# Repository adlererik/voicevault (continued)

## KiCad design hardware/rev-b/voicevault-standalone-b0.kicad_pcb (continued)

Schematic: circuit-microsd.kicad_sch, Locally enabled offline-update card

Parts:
C401: 2.2u 10V; C_0603_1608Metric
C402: 10u 10V; C_0805_2012Metric
C403, C404, C405: 100n 10V; C_0402_1005Metric
J401: 1040310811; microSD_HC_Molex_104031-0811
R401, R402: 100k; R_0402_1005Metric
R403, R404, R405, R406, R407: 47k; R_0402_1005Metric
U401: TLV75533PDRVR; TI_DRV0006A_WSON6_2x2_EP1x1p6
U402: SN74AXC4T774PWR; TSSOP-16_4.4x5mm_P0.65mm

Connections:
GND: C401.2, C402.2, C403.2, C404.2, C405.2, J401.6 (VSS), J401.10 (DETECT_GND), J401.SH (SHELL), R401.2, U401.3 (GND), U401.7 (EP_GND), U402.7 (DIR3), U402.10 (GND); also elsewhere on the board
SD_3V3: C402.1, C403.1, C405.1, J401.4 (VDD), R403.2, R404.2, R405.2, R406.2, U401.1 (OUT), U402.15 (VCCB); also elsewhere on the board
SD_CS_MCU: U402.6 (A4); also elsewhere on the board
SD_CS_N: J401.2 (DAT3_CS), R403.1, U402.11 (B4)
SD_DAT1: J401.8 (DAT1), R404.1
SD_DAT2: J401.1 (DAT2), R405.1
SD_DETECT_N: J401.9 (DETECT), R407.1; also elsewhere on the board
SD_IO_DISABLE: R402.1, U402.9 (OE_N); also elsewhere on the board
SD_MISO: J401.7 (DAT0_MISO), U402.12 (B3)
SD_MISO_MCU: U402.5 (A3); also elsewhere on the board
SD_MOSI: J401.3 (CMD_MOSI), R406.1, U402.13 (B2)
SD_MOSI_MCU: U402.4 (A2); also elsewhere on the board
SD_POWER_EN: R401.1, U401.4 (EN); also elsewhere on the board
SD_SCK: J401.5 (CLK), U402.14 (B1)
SD_SCK_MCU: U402.3 (A1); also elsewhere on the board
VDD_3V3: C404.1, R402.2, R407.2, U402.1 (DIR1), U402.2 (DIR2), U402.8 (DIR4), U402.16 (VCCA); also elsewhere on the board
VSYS: C401.1, U401.6 (IN); also elsewhere on the board

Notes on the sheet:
Card uses software SPI on dedicated MCU GPIO; no radio/shared trusted bus access.
Power and signal bridge default off. Enable card power, verify settle, then enable signals only in local update mode.
Reject unsigned, wrong-target and rollback images on the trusted MCU; card data remains untrusted.
LDO is specified for 500mA but thermal/current/battery limits and card peak current still require bench qualification.
Card-detect switch stays in trusted 3.3V domain; it is mechanically isolated from SD power.

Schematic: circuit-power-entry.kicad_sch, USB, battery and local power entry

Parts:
C501: 100n 16V; C_0402_1005Metric
C502: 100n 10V; C_0402_1005Metric
D501, D502: PMEG2010ER,115; Nexperia_CFP3_SOD-123W
D503: SMF5.0A; D_SOD-123F
F501: MF-PSMF050X-2; Fuse_0805_2012Metric
J501: USB4125-GF-A; USB_C_Receptacle_GCT_USB4125-xx-x_6P_TopMnt_Horizontal
J502: S2B-PH-SM4-TB(LF)(SN); BATTERY; JST_PH_S2B-PH-SM4-TB_1x02-1MP_P2.00mm_Horizontal
J503: BM02B-SRSS-TB(LF)(SN); EXTERNAL NTC; JST_SH_BM02B-SRSS-TB_1x02-1MP_P1.00mm_Vertical
SW503: TL3305AF160QG; POWER; SW_SPST_TL3305A

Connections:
BAT_NTC: J503.1 (NTC); also elsewhere on the board
BAT_PACK: C502.1, J502.1 (PACK_PLUS); also elsewhere on the board
BTN_POWER: SW503.1 (SHPHLD); also elsewhere on the board
GND: C501.2, C502.2, D503.2 (A), J501.A12 (GND), J501.B12 (GND), J501.SH (SHELL), J502.2 (PACK_MINUS), J503.2 (GND), SW503.2 (GND); also elsewhere on the board
PMIC_VBUS: C501.1, D501.1 (K), D502.1 (K); also elsewhere on the board
QI_5V: D502.2 (A); also elsewhere on the board
USB_5V_FUSED: D501.2 (A), D503.1 (K), F501.2 (OUT)
USB_5V_RAW: F501.1 (IN), J501.A9 (VBUS), J501.B9 (VBUS)
USB_CC1: J501.A5 (CC1); also elsewhere on the board
USB_CC2: J501.B5 (CC2); also elsewhere on the board

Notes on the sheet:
USB4125 has power/CC only: no USB data connection to trusted MCU. Power USB is for a trusted bench source.
USB/Qi Schottky OR prevents direct source paralleling; input allowance includes voltage drop, fuse derating and heat.
nPM1300 supplies CC pull-downs internally; do not add parallel 5.1k resistors.
External 10k NTC with configured beta must be thermally attached to the battery. Missing/invalid NTC must inhibit charging.
Battery is a protected external assembly. Verify actual connector polarity before power; no battery included in PCB assembly BOM.

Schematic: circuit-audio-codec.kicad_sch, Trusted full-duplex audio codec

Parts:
C601, C602, C603, C605: 10u 10V; C_0805_2012Metric
C604, C606, C607, C608: 100n 10V; C_0402_1005Metric
D601: BAT54WS; DLDO to ALDO pop suppression; D_SOD-323
R601, R602: 2.2k; R_0402_1005Metric
R603: 100k; R_0402_1005Metric
U601: TLV320AIC3204IRHBR; QFN-32-1EP_5x5mm_P0.5mm_EP3.45x3.45mm

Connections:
AUD_ADC_DATA: U601.5 (DOUT); also elsewhere on the board
AUD_AVDD_1V8: C601.1, C607.1, D601.1 (K), U601.24 (AVDD_ALDO_OUT)
AUD_BCLK: U601.2 (BCLK); also elsewhere on the board
AUD_DAC_DATA: U601.4 (DIN); also elsewhere on the board
AUD_DVDD_1V72: C602.1, C608.1, D601.2 (A), U601.29 (DVDD_DLDO_OUT)
AUD_HPL_DC: U601.25 (HPL); also elsewhere on the board
AUD_HPR_DC: U601.27 (HPR); also elsewhere on the board
AUD_LDOIN_3V3: C605.1, C606.1, U601.26 (LDOIN_HPVDD); also elsewhere on the board
AUD_MCLK: U601.1 (MCLK); also elsewhere on the board
AUD_MICBIAS: U601.19 (MICBIAS); also elsewhere on the board
AUD_REF: C603.1, U601.18 (REF)
AUD_RESET_N: R603.1, U601.31 (RESET_N); also elsewhere on the board
AUD_SCL: R601.1, U601.9 (SCL); also elsewhere on the board
AUD_SDA: R602.1, U601.10 (SDA); also elsewhere on the board
AUD_WCLK: U601.3 (WCLK); also elsewhere on the board
GND: C601.2, C602.2, C603.2, C604.2, C605.2, C606.2, C607.2, C608.2, R603.2, U601.7 (IOVSS), U601.8 (SCLK_MFP3), U601.12 (SPI_SELECT_I2C), U601.17 (AVSS), U601.28 (DVSS), U601.33 (EP_GND); also elsewhere on the board
MIC_ADC: U601.13 (IN1_L); also elsewhere on the board
VDD_3V3: C604.1, R601.2, R602.2, U601.6 (IOVDD), U601.30 (LDO_SELECT_INTERNAL); also elsewhere on the board

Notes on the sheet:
TI SLOS602E pins/package; SLAA492A internal DLDO/ALDO sequence with DVDD-to-AVDD Schottky diode.
IOVDD uses VDD_3V3; LDOIN has a separate switched 500mA-capable regulator. LDO_SELECT high enables internal 1.72V DLDO; AVDD/DVDD are not tied to 3.3V.
Hold RESET low while rails settle; wait at least 1ms after reset before writes, enable ALDO at >=DLDO voltage, then ADC/DAC.
SAI1 AF13: PE2 MCLK_A, PE3 SD_B capture, PE4 FS_A, PE5 SCK_A, PE6 SD_A playback.
Audio I2C2 PF0/PF1 and SAI are connected only to the trusted MCU; no radio wires.

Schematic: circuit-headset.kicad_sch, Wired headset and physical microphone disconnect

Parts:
C609: 1u 10V X7R; C_0603_1608Metric
C610: 33p C0G; C_0402_1005Metric
C611, C612: 220u 6.3V polymer; exact MPN qualification pending; CP_EIA-7343-31_Kemet-D
D602, D603, D604: PESD5V0S1BA,115; bidirectional ESD; D_SOD-323
J601: SJ-43514-SMT-TR; CTIA headset; SJ43514SMT
R604: 2.2k 1%; R_0402_1005Metric
R605: 1k 1%; R_0402_1005Metric
R606, R607: 10R 1% 0.1W; R_0402_1005Metric
SW601: JS102011SAQN; physical microphone disconnect; SW_SPDT_CK_JS102011SAQN

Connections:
AUD_HPL_DC: C611.1 (PLUS); also elsewhere on the board
AUD_HPR_DC: C612.1 (PLUS); also elsewhere on the board
AUD_MICBIAS: R604.1; also elsewhere on the board
GND: C610.2, D602.2 (RETURN), D603.2 (RETURN), D604.2 (RETURN), J601.4 (RING2_GND), SW601.3 (MUTE_GROUND); also elsewhere on the board
HEADSET_L: D602.1 (LINE), J601.2 (TIP_LEFT), R606.2
HEADSET_MIC: D604.1 (LINE), J601.1 (SLEEVE_MIC), SW601.1 (TALK)
HEADSET_R: D603.1 (LINE), J601.3 (RING1_RIGHT), R607.2
HP_L_AC: C611.2 (MINUS), R606.1
HP_R_AC: C612.2 (MINUS), R607.1
MIC_ADC: C609.2, C610.1; also elsewhere on the board
MIC_BIASED: R604.2, R605.1, SW601.2 (COMMON)
MIC_COUPLE: C609.1, R605.2

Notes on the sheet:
CTIA only: Tip L, ring1 R, ring2 GND, sleeve MIC. OMTP requires an external passive adapter.
Mute switch disconnects headset microphone and grounds codec-side input; bias is after the disconnect.
No built-in microphone or speaker. Headphone outputs are independently AC coupled; never short HPL/HPR together.
220u coupling and 10R series values are evaluated in SPICE; exact capacitor MPN and headset/audio quality need qualification.
ESD parts are protective design elements, not a claim of tested IEC immunity.

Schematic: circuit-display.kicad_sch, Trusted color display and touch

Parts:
C701: 4.7u 10V; C_0603_1608Metric
C702: 100n 10V; C_0402_1005Metric
C703: 1u 10V; C_0603_1608Metric
J701: FH12-40S-0.5SH(55); TFT FFC; Hirose_FH12-40S-0.5SH_1x40-1MP_P0.50mm_Horizontal
J702: 2005280060; TOUCH FFC; Molex_200528-0060_1x06-1MP_P1.00mm_Horizontal
R701, R702: 4.7k; R_0402_1005Metric
R703, R704: 100k; R_0402_1005Metric
R705, R706: 47k; R_0402_1005Metric

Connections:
BL_ANODE: J701.38 (LED_A); also elsewhere on the board
BL_K1: J701.34 (LED_K1); also elsewhere on the board
BL_K2: J701.35 (LED_K2); also elsewhere on the board
BL_K3: J701.36 (LED_K3); also elsewhere on the board
BL_K4: J701.37 (LED_K4); also elsewhere on the board
GND: C701.2, C702.2, C703.2, J701.1 (GND), J701.12 (WRX_UNUSED), J701.13 (RDX_UNUSED), J701.14 (DB0), J701.15 (DB1), J701.16 (DB2), J701.17 (DB3), J701.18 (DB4), J701.19 (DB5), J701.20 (DB6), J701.21 (DB7), J701.22 (DB8), J701.23 (DB9), J701.24 (DB10), J701.25 (DB11), J701.26 (DB12), J701.27 (DB13), J701.28 (DB14), J701.29 (DB15), J701.33 (GND), J701.39 (GND), J702.2 (VSS), R703.2, R704.2; also elsewhere on the board
LCD_CS_N: J701.10 (CSX), R705.1; also elsewhere on the board
LCD_RESET_N: J701.30 (RESX), R703.1; also elsewhere on the board
LCD_SCK: J701.11 (DCX_SCL); also elsewhere on the board
LCD_SDI: J701.9 (SDA); also elsewhere on the board
LCD_SDO: J701.6 (SDO); also elsewhere on the board
LCD_TE: J701.40 (TE); also elsewhere on the board
TOUCH_IRQ_N: J702.5 (INT_N), R706.1; also elsewhere on the board
TOUCH_RESET_N: J702.6 (RESET_N), R704.1; also elsewhere on the board
TOUCH_SCL: J702.3 (SCL), R701.1; also elsewhere on the board
TOUCH_SDA: J702.4 (SDA), R702.1; also elsewhere on the board
VDD_3V3: C701.1, C702.1, C703.1, J701.7 (VDD), J701.8 (VDDI), J701.31 (IM0_SPI), J701.32 (IM2_SPI), J702.1 (VDD), R701.2, R702.2, R705.2, R706.2; also elsewhere on the board

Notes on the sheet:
Newhaven NHD-2.4-240320AF-CTXP-CTP: 3-wire, 9-bit SPI3; IM0/IM2 high. Unused WR/RD/DB grounded per module wiring diagram.
IOVDD/LCD/touch use trusted MCU rail; hold both resets low until firmware confirms 3.3V.
Touch uses I2C5 PD0/PD1 AF4, separate from power, audio and secure-element buses.
Connector equivalents are bottom-contact 40x0.5mm and 6x1.0mm. Verify actual flex thickness, pin-1 and bend clearance.
Display is a separately procured assembly, not an IC mounted by the board assembler.

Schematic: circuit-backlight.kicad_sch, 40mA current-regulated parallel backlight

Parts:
C704: 2.2u 10V; C_0603_1608Metric
C705: 1u 50V X7R; C_0805_2012Metric
D701: BZT52H-C6V2,115; open-load clamp; D_SOD-123F
L701: SRN4018-220M / 22uH; L_Bourns-SRN4018
R707: 12R 1% 0.1W; R_0402_1005Metric
R708: 100k; R_0402_1005Metric
R709, R710, R711, R712: 200R 1% 0.25W; R_0805_2012Metric
U9: TPS61062YZFR; TPS61062_YZF8_REVIEW

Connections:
BACKLIGHT_PWM: R708.1, U9.A2 (EN); also elsewhere on the board
BL_ANODE: C705.1, D701.1 (K), U9.C1 (OUT); also elsewhere on the board
BL_FB: D701.2 (A), R707.1, R709.2, R710.2, R711.2, R712.2, U9.B3 (FB)
BL_K1: R709.1; also elsewhere on the board
BL_K2: R710.1; also elsewhere on the board
BL_K3: R711.1; also elsewhere on the board
BL_K4: R712.1; also elsewhere on the board
BL_SW: L701.2, U9.C2 (SW)
GND: C704.2, C705.2, R707.2, R708.2, U9.A1 (GND), U9.A3 (ILED_500mV), U9.C3 (PGND); also elsewhere on the board
VSYS: C704.1, L701.1, U9.B1 (VIN); also elsewhere on the board

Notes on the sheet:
TPS61062 constant-current mode: ILED grounded, 0.5V / 12R = 41.7mA nominal total; tolerance minimum 40.0mA.
Four 200R / 0.25W ballast resistors share branch current; include zener-clamp and open-LED fault sensitivity.
Boost input is VSYS directly; its worst-case current exceeds the PMIC load-switch 100mA rating. AUX buck budget remains a gate.
PWM at <=1kHz, default-low EN. Initial total backlight current is approximately 42mA.
6.2V zener provides alternate feedback path on open load; output capacitor is rated 50V for device OVP.
YZF land-pattern geometry still needs exact manufacturer package-drawing review; do not release fabrication.
Input is raw VSYS (2.7-6V driver range), with full operation gated at VSYS >=3.6V pending bench qualification; do not use the MCU/AUX buck for boost input.

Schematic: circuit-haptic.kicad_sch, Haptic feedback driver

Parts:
C801, C802: 100n 10V; C_0402_1005Metric
C803: 10u 10V; C_0805_2012Metric
J801: BM02B-SRSS-TB(LF)(SN); LRA; JST_SH_BM02B-SRSS-TB_1x02-1MP_P1.00mm_Vertical
R801: 100k; R_0402_1005Metric
R802: 47k; R_0402_1005Metric
U10: DRV2624YFFR; DRV2624_YFF9

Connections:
GND: C801.2, C802.2, C803.2, R801.2, U10.B3 (GND); also elsewhere on the board
HAPTIC_IRQ_N: R802.1, U10.A1 (TRIG_INT_N); also elsewhere on the board
HAPTIC_MINUS: J801.2 (LRA_MINUS), U10.C3 (OUT_MINUS)
HAPTIC_PLUS: J801.1 (LRA_PLUS), U10.A3 (OUT_PLUS)
HAPTIC_REG: C802.1, U10.A2 (REG)
HAPTIC_RESET_N: R801.1, U10.B2 (NRST); also elsewhere on the board
PMIC_SCL: U10.C1 (SCL); also elsewhere on the board
PMIC_SDA: U10.B1 (SDA); also elsewhere on the board
VDD_3V3: R802.2; also elsewhere on the board
VSYS: C801.1, C803.1, U10.C2 (VDD); also elsewhere on the board

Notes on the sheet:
DRV2624 9-ball YFF map and 0.225mm pad / 0.4mm pitch from TI SLOS893D package drawing.
Actuator is an external LRA assembly. Its exact MPN, rated drive and auto-calibration settings remain qualification gates.
NRST defaults low; no startup vibration. Use I2C address 0x5A on trusted power-control bus.

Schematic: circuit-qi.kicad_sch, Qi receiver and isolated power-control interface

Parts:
C901, C902: 100n 50V X7R; C_0805_2012Metric
C903: 47n 50V X7R; C_0805_2012Metric
C904: 1n 50V C0G; C_0603_1608Metric
C905, C906: 47n 50V; C_0603_1608Metric
C907, C908: 22n 50V; C_0603_1608Metric
C909, C910: 10n 50V; C_0603_1608Metric
C911: 4.7u 10V; C_0603_1608Metric
C912: 1u 10V; C_0603_1608Metric
C913, C914, C915, C916: 10u 25V X5R; C_0805_2012Metric
C917, C918: 100n 25V; C_0603_1608Metric
D903, D904: SMF13A; D_SOD-123F
J901: BM02B-SRSS-TB(LF)(SN); 760308101219 COIL; JST_SH_BM02B-SRSS-TB_1x02-1MP_P1.00mm_Vertical
R907, R908: ERJ-P08F2000V / 200R surge; R_1206_3216Metric
U5: STWLC38JRM; STWLC38_WLCSP40_REVIEW

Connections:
GND: C911.2, C912.2, C913.2, C914.2, C915.2, C916.2, C917.2, C918.2, D903.2 (A), D904.2 (A), U5.A1 (VSSP), U5.A2 (VSSP), U5.A4 (VSSP), U5.A5 (VSSP), U5.E5 (VSSA), U5.F5 (VSSD); also elsewhere on the board
QI_5V: C915.1, C916.1, C917.1, U5.E1 (VOUT), U5.E2 (VOUT_PARALLEL); also elsewhere on the board
QI_AC1: C901.2, C902.2, C903.2, C904.1, C905.2, C907.2, C909.2, D903.1 (K), U5.B4 (AC1), U5.B5 (AC1), U5.C4 (AC1), U5.C5 (AC1)
QI_AC2: C904.2, C906.2, C908.2, C910.2, D904.1 (K), J901.2 (COIL_B), U5.B1 (AC2), U5.B2 (AC2), U5.C1 (AC2), U5.C2 (AC2)
QI_BOOT1: C905.1, U5.B3 (BOOT1)
QI_BOOT2: C906.1, U5.C3 (BOOT2)
QI_COIL_A: C901.1, C902.1, C903.1, J901.1 (COIL_A); also elsewhere on the board
QI_COMA1: C907.1, U5.G1 (COMA1)
QI_COMA2: C908.1, U5.G2 (COMA2)
QI_COMB1: C909.1, U5.H1 (COMB1)
QI_COMB2: C910.1, U5.H2 (COMB2)
QI_ENB: U5.G4 (ENB); also elsewhere on the board
QI_IEXT: R907.2, R908.2, U5.A3 (IEXT)
QI_IRQ_N: U5.H4 (INTB); also elsewhere on the board
QI_NTC: U5.F1 (NTC); also elsewhere on the board
QI_SCL: U5.H5 (SCL); also elsewhere on the board
QI_SDA: U5.G5 (SDA); also elsewhere on the board
QI_VAA_2V5: C911.1, U5.E4 (VAA); also elsewhere on the board
QI_VDD_1V1: C912.1, U5.F4 (VDD)
QI_VRECT: C913.1, C914.1, C918.1, R907.1, R908.1, U5.D1 (VRECT), U5.D2 (VRECT), U5.D3 (VRECT), U5.D4 (VRECT), U5.D5 (VRECT)
QI_VS: U5.F2 (VS); also elsewhere on the board

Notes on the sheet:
ST DS14078 Rev1 Table37 wearable reference; catalogue coil 760308101219 (11.8uH), 247n series, 1n parallel.
Qi I2C is software-driven on PD3/PD4, physically separate from PMIC/secure-element buses. Bound every transaction and timeout.
Configure and read back 5.0V RX output; no reverse-transmit mode. nPM1300 input OVP rejects excessive output voltage.
See Qi sensing/control sheet for separate control bus, thermistor and ASK filter.
Coil/charger/metal-stack tuning, FOD, thermal, surge and layout qualification are still required.

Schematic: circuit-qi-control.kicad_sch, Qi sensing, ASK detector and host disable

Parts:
C919: 3.3n 50V; C_0603_1608Metric
C920: 22n 50V; C_0603_1608Metric
C921: 1.5n 50V; C_0603_1608Metric
C922: 1n 10V; C_0402_1005Metric
D901, D902: 1N4148WS-7-F; D_SOD-323
J902: BM02B-SRSS-TB(LF)(SN); COIL NTC; JST_SH_BM02B-SRSS-TB_1x02-1MP_P1.00mm_Vertical
Q901: AO3401A (AOS); SOT-23
Q902: 2N7002; SOT-23
R901, R904: 10k 1%; R_0402_1005Metric
R902: 6.8k 1%; R_0402_1005Metric
R903: 220k 1%; R_0402_1005Metric
R905: 150k 1%; R_0402_1005Metric
R906: 100k 1%; R_0402_1005Metric
R909, R910: 2.2k; R_0402_1005Metric
R911: 47k; R_0402_1005Metric
R912, R913, R914: 100k; R_0402_1005Metric

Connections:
GND: C919.2, C921.2, C922.2, D902.2 (A), J902.2 (RETURN), Q902.2 (S), R903.2, R906.2, R913.2, R914.2; also elsewhere on the board
QI_COIL_A: D901.2 (A); also elsewhere on the board
QI_DEMOD_COUPLE: C920.1, R904.2
QI_DEMOD_FILTER: C919.1, R902.2, R903.1, R904.1
QI_DEMOD_RAW: D901.1 (K), R902.1
QI_DISABLE: Q902.1 (G), R914.1; also elsewhere on the board
QI_ENB: Q901.3 (D), R913.1; also elsewhere on the board
QI_EN_GATE: Q901.1 (G), Q902.3 (D), R912.1
QI_IRQ_N: R911.1; also elsewhere on the board
QI_NTC: C922.1, J902.1 (10k_NTC), R901.2; also elsewhere on the board
QI_SCL: R909.1; also elsewhere on the board
QI_SDA: R910.1; also elsewhere on the board
QI_VAA_2V5: Q901.2 (S), R901.1, R905.1, R912.2; also elsewhere on the board
QI_VS: C920.2, C921.1, D902.1 (K), R905.2, R906.1; also elsewhere on the board
VDD_3V3: R909.2, R910.2, R911.2; also elsewhere on the board

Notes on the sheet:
Qi control bus is separate from PMIC and secure-element buses; bound transactions and timeouts.
NTC must be attached to the coil. Divider and actual thermal cutoff must be bench-qualified.
Two-FET ENB circuit defaults to autonomous startup and avoids driving an unpowered chip from the MCU rail.
ASK detector follows ST DS14078 Figure15; 1N4148WS substitutes the reference signal diode and needs bench comparison.

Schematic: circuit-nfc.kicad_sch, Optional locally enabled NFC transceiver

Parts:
C1001, C1003, C1007, C1009, C1016: 2.2u 10V; C_0603_1608Metric
C1002: 100n 10V; C_0402_1005Metric
C1004, C1006, C1008, C1010, C1013: 10n 10V; C_0402_1005Metric
C1005: 4.7u 10V; C_0603_1608Metric
C1011: 22n 10V; C_0402_1005Metric
C1012: 1u 10V; C_0603_1608Metric
C1014, C1015: 10p C0G; C_0402_1005Metric
R1001: 100k; R_0402_1005Metric
R1002: 47k; R_0402_1005Metric
U7: ST25R3916B-BWLT; ST25R3916B_WLCSP36_REVIEW
U1001: TLV75533PDRVR; TI_DRV0006A_WSON6_2x2_EP1x1p6
X1001: 830108212709 / 27.12MHz CL8pF; Crystal_SMD_2016-4Pin_2.0x1.6mm

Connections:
GND: C1001.2, C1002.2, C1003.2, C1004.2, C1005.2, C1006.2, C1007.2, C1008.2, C1009.2, C1010.2, C1011.2, C1012.2, C1013.2, C1014.2, C1015.2, C1016.2, R1001.2, U7.A3 (GND_A), U7.B3 (GND_A), U7.B4 (GND_A), U7.C1 (VSS), U7.C2 (VSS), U7.C3 (VSS), U7.D2 (I2C_EN), U7.D5 (GND_D), U7.F1 (GND_DR2), U7.F4 (GND_DR1), U1001.3 (GND), U1001.7 (EP_GND), X1001.2 (CASE), X1001.4 (CASE); also elsewhere on the board
NFC_3V3: C1001.1, C1002.1, C1003.1, C1004.1, R1002.2, U7.A6 (VDD_IO), U7.E5 (VDD_TX), U7.E6 (VDD), U1001.1 (OUT); also elsewhere on the board
NFC_AGDC: C1012.1, C1013.1, U7.A2 (AGDC)
NFC_CS_N: R1002.1, U7.A5 (BSS); also elsewhere on the board
NFC_IRQ: U7.A4 (IRQ); also elsewhere on the board
NFC_MISO: U7.B5 (MISO); also elsewhere on the board
NFC_MOSI: U7.D4 (MOSI); also elsewhere on the board
NFC_POWER_EN: R1001.1, U1001.4 (EN); also elsewhere on the board
NFC_RFI1: U7.B1 (RFI1); also elsewhere on the board
NFC_RFI2: U7.B2 (RFI2); also elsewhere on the board
NFC_RFO1: U7.F3 (RFO1); also elsewhere on the board
NFC_RFO2: U7.F2 (RFO2); also elsewhere on the board
NFC_RF_DR: C1005.1, C1006.1, U7.E3 (VDD_DR), U7.F6 (VDD_RF)
NFC_SCK: U7.D3 (SCLK); also elsewhere on the board
NFC_VDD_A: C1009.1, C1010.1, U7.E4 (VDD_A)
NFC_VDD_AM: C1011.1, U7.F5 (VDD_AM)
NFC_VDD_D: C1007.1, C1008.1, U7.C5 (VDD_D)
NFC_XTI: C1014.1, U7.D6 (XTI), X1001.1 (XI)
NFC_XTO: C1015.1, U7.C6 (XTO), X1001.3 (XO)
VSYS: C1016.1, U1001.6 (IN); also elsewhere on the board

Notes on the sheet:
ST25R3916B-BWLT retains Safe7 core part. Supplies/decoupling and crystal follow pinned TS7 sheet10 and ST DS13541.
Dedicated VSYS LDO avoids overloading the MCU 200mA buck. Default power off and signal bridge disabled.
No NFC use during calls or charging tests until RF/thermal/current limits and trusted local pairing are defined.
IRQ is active HIGH. TAD/clock/automatic-tuning outputs unused. Fixed matching network is on the following sheet.
NFC transport alone does not authenticate a contact; device signatures/pinned contacts and local confirmation remain mandatory.

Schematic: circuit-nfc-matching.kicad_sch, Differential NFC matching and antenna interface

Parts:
C1017, C1018: 680p C0G 50V; C_0402_1005Metric
C1019, C1020: 150p C0G 50V; C_0402_1005Metric
C1021, C1022: 68p C0G 50V; C_0402_1005Metric
C1023, C1024: 10p C0G 50V; C_0402_1005Metric
C1025, C1026: 180p C0G 50V; C_0402_1005Metric
J1001: BM02B-SRSS-TB(LF)(SN); NFC ANTENNA; JST_SH_BM02B-SRSS-TB_1x02-1MP_P1.00mm_Vertical
L1001, L1002: 270nH RF; L_0603_1608Metric
R1003, R1004: 2R 1%; R_0402_1005Metric

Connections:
GND: C1017.2, C1018.2, C1021.2, C1022.2, C1025.2, C1026.2; also elsewhere on the board
NFC_ANT1: J1001.1 (ANT_1), R1003.2
NFC_ANT2: J1001.2 (ANT_2), R1004.2
NFC_EMC1: C1017.1, C1019.1, L1001.2
NFC_EMC2: C1018.1, C1020.1, L1002.2
NFC_MATCH1: C1019.2, C1021.1, C1023.1, R1003.1
NFC_MATCH2: C1020.2, C1022.1, C1024.1, R1004.1
NFC_RFI1: C1023.2, C1025.1; also elsewhere on the board
NFC_RFI2: C1024.2, C1026.1; also elsewhere on the board
NFC_RFO1: L1001.1; also elsewhere on the board
NFC_RFO2: L1002.1; also elsewhere on the board

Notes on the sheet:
Matching topology/starting values from Safe7 TS7 revD sheet10. They are NOT validated for a replacement antenna.
Pulse W7001 is a catalogue antenna candidate; confirm supply, dimensions, inductance/Q and cable before release.
Require VNA matching, field strength, coexistence, ferrite/metal-stack and temperature tests on the actual assembly.
Keep NFC disabled until antenna/current/thermal and pairing-protocol qualification passes.

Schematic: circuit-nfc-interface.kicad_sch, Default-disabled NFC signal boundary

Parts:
C1027, C1028, C1029, C1030: 100n 10V; C_0402_1005Metric
R1005, R1006: 100k; R_0402_1005Metric
U1002, U1003: SN74AXC4T774PWR; TSSOP-16_4.4x5mm_P0.65mm

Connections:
GND: C1027.2, C1028.2, C1029.2, C1030.2, R1006.2, U1002.7 (DIR3), U1002.10 (GND), U1003.1 (DIR1), U1003.4 (A2), U1003.5 (A3), U1003.6 (A4), U1003.10 (GND); also elsewhere on the board
NFC_3V3: C1028.1, C1030.1, U1002.15 (VCCB), U1003.15 (VCCB); also elsewhere on the board
NFC_CS_N: U1002.11 (B4); also elsewhere on the board
NFC_HOST_CS_N: U1002.6 (A4); also elsewhere on the board
NFC_HOST_IRQ: R1006.1, U1003.3 (A1); also elsewhere on the board
NFC_HOST_MISO: U1002.5 (A3); also elsewhere on the board
NFC_HOST_MOSI: U1002.4 (A2); also elsewhere on the board
NFC_HOST_SCK: U1002.3 (A1); also elsewhere on the board
NFC_IO_DISABLE: R1005.1, U1002.9 (OE_N), U1003.9 (OE_N); also elsewhere on the board
NFC_IRQ: U1003.14 (B1); also elsewhere on the board
NFC_MISO: U1002.12 (B3); also elsewhere on the board
NFC_MOSI: U1002.13 (B2); also elsewhere on the board
NFC_SCK: U1002.14 (B1); also elsewhere on the board
VDD_3V3: C1027.1, C1029.1, R1005.2, U1002.1 (DIR1), U1002.2 (DIR2), U1002.8 (DIR4), U1002.16 (VCCA), U1003.2 (DIR2), U1003.7 (DIR3), U1003.8 (DIR4), U1003.16 (VCCA); also elsewhere on the board

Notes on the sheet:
SPI1 PA5/PA6/PA7, GPIO PA4 CS, PG9 active-high IRQ; no shared radio, secure-element or PMIC bus.
Strapped directions and default-high OE keep NFC signals disconnected through reset and power changes.
Check VCC isolation, power-off leakage and interrupt-flood bounds on the assembled prototype.

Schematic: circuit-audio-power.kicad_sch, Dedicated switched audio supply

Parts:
C614, C615: 2.2u 10V; C_0603_1608Metric
R608: 100k; R_0402_1005Metric
R609: 0R - removable audio-current link; R_0603_1608Metric
U602: TLV75533PDRVR; TI_DRV0006A_WSON6_2x2_EP1x1p6

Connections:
AUD_3V3_REG: C615.1, R609.1, U602.1 (OUT)
AUD_LDOIN_3V3: R609.2; also elsewhere on the board
AUD_POWER_EN: R608.1, U602.4 (EN); also elsewhere on the board
GND: C614.2, C615.2, R608.2, U602.3 (GND), U602.7 (EP_GND); also elsewhere on the board
VSYS: C614.1, U602.6 (IN); also elsewhere on the board

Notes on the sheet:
Do not place the codec analog/headphone supply on the 200mA MCU buck: TI calls for 150mA analog capability plus digital demand.
PB10 enable has a 100k pulldown. IOVDD must be valid before LDOIN; hold audio RESET and clocks low during startup.
After MCU rail/configuration readback, enable LDOIN; verify rail and internal DLDO, then release RESET and wait >=1ms before writes.
R609 is a removable current-measurement link. VSYS dropout and output discharge/restart require bench tests.
DRV WSON thermal pad must connect to ground/copper heat spreading; 500mA rating is not a continuous thermal allocation.
The TLV755 input/output capacitors must retain >0.47uF effective capacitance after DC bias, tolerance and temperature.

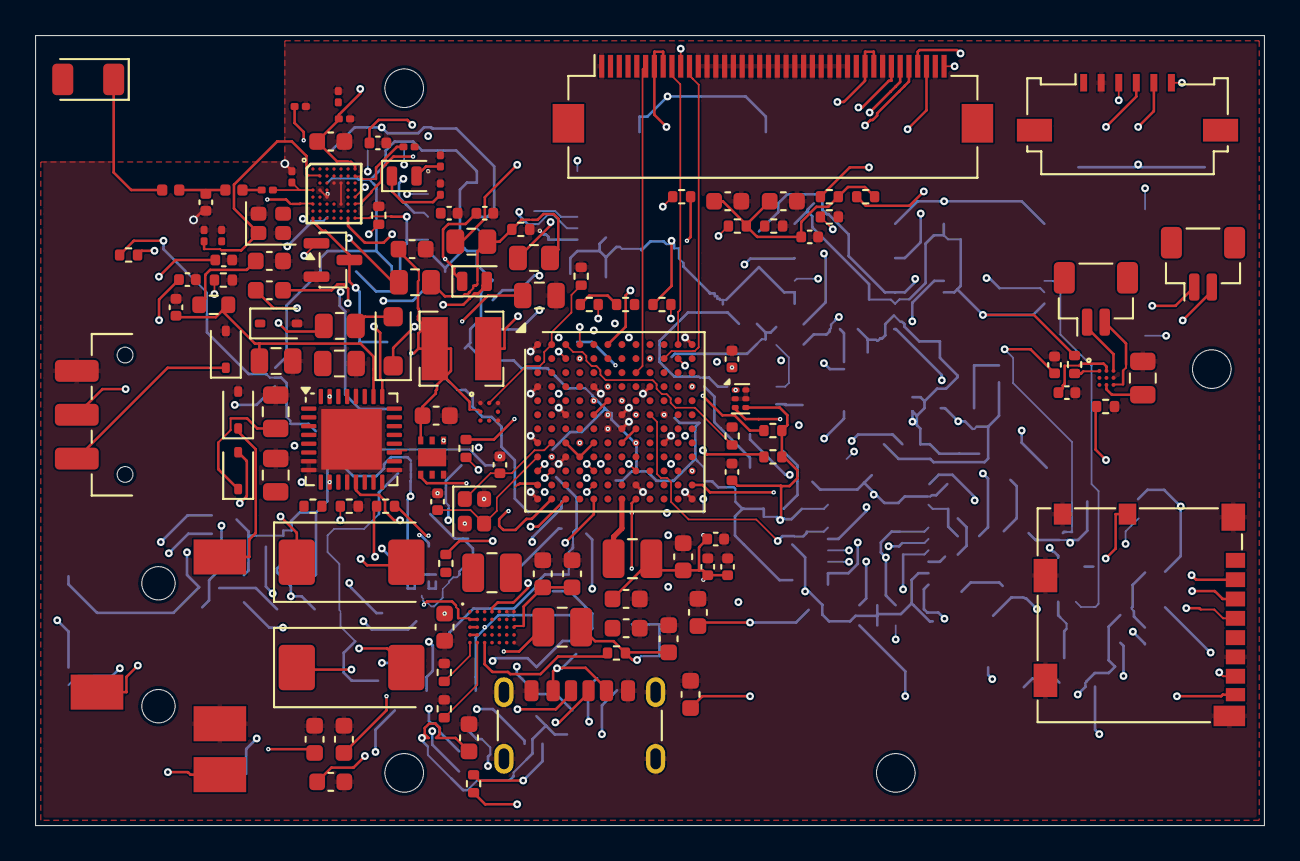
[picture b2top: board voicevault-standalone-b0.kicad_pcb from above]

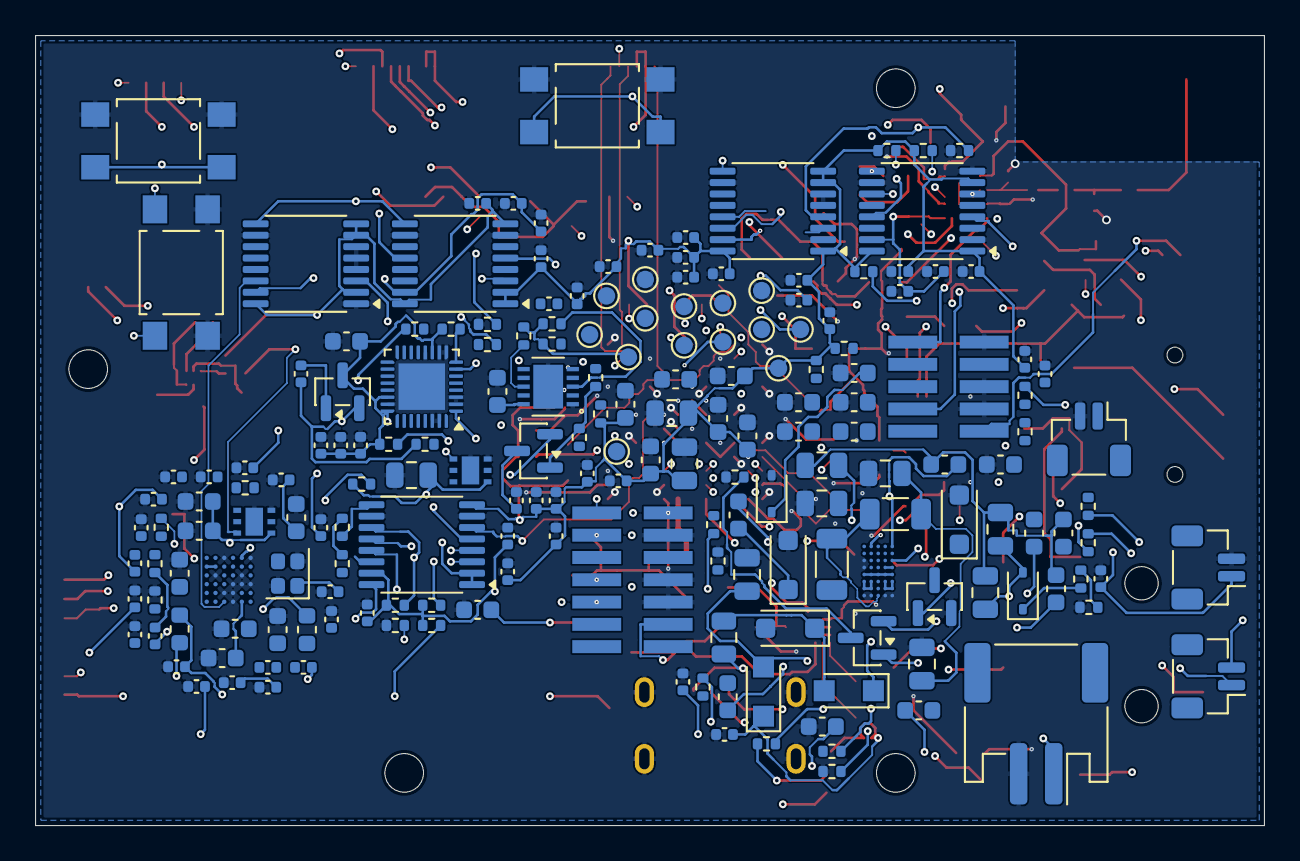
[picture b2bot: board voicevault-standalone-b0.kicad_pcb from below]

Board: 6 copper layers, 70.0 x 45.0 mm, 314 parts (189 on the bottom side), 199 nets.

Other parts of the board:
H1, H2, H3, H4: M2 mounting hole / not an assembled component; MountingHole_2.2mm_M2
TP1: PROBE VSYS; TestPoint_Pad_D1.0mm
TP2, TP14: PROBE GND; TestPoint_Pad_D1.0mm
TP3: PROBE VDD_3V3; TestPoint_Pad_D1.0mm
TP4: PROBE AUX_3V3; TestPoint_Pad_D1.0mm
TP5: PROBE MCU_VDD11; TestPoint_Pad_D1.0mm
TP6: PROBE RADIO_3V3; TestPoint_Pad_D1.0mm
TP7: PROBE TR_3V3; TestPoint_Pad_D1.0mm
TP8: PROBE OP_3V3; TestPoint_Pad_D1.0mm
TP9: PROBE SD_3V3; TestPoint_Pad_D1.0mm
TP10: PROBE NFC_3V3; TestPoint_Pad_D1.0mm
TP11: PROBE AUD_LDOIN_3V3; TestPoint_Pad_D1.0mm
TP12: PROBE QI_5V; TestPoint_Pad_D1.0mm
TP13: PROBE BAT_PACK; TestPoint_Pad_D1.0mm

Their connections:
AUD_LDOIN_3V3: TP11.1; also elsewhere on the board
AUX_3V3: TP4.1; also elsewhere on the board
BAT_PACK: TP13.1; also elsewhere on the board
GND: TP2.1, TP14.1; also elsewhere on the board
MCU_VDD11: TP5.1; also elsewhere on the board
NFC_3V3: TP10.1; also elsewhere on the board
OP_3V3: TP8.1; also elsewhere on the board
QI_5V: TP12.1; also elsewhere on the board
RADIO_3V3: TP6.1; also elsewhere on the board
SD_3V3: TP9.1; also elsewhere on the board
TR_3V3: TP7.1; also elsewhere on the board
VDD_3V3: TP3.1; also elsewhere on the board
VSYS: TP1.1; also elsewhere on the board

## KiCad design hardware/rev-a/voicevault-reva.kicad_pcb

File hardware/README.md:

# VoiceVault hardware laboratory

The active new hardware revision is **[VoiceVault C1, STM32U5G9ZJT6Q LQFP144](rev-c1/README.md)**. Its clean [Quilter full-layout run](https://app.quilter.ai/jobs/6afb49addfae511781423d99?candidate=3) finished at **21:19 CET on 16 November 2026**, with six 98% candidates. Independent review of 3.1 confirms six missing connections and zero copper shorts, with hole-clearance/antenna/placement issues remaining. [Returned PCB views and native reports](evidence/2026-11-17/c1-return-review/README.md). C1 has 199 electrical components, 13 probes and four mounting holes (216 footprints). The corrected MCU package/power mapping and PB13 microSD clock pass native ERC, pin/function and schematic-parity checks. The original cloud input contains no previous copper. The owner subsequently authorized [local repairs](rev-c1/local-repair-03/README.md), which remain incomplete. [Front and back CAD renders](visuals/2026-11-17/README.md) show the checked layout with some approximate component bodies. [Native, RF, SPICE and cloud-input evidence](evidence/2026-11-16/c1-preparation/README.md).

The simplified architecture retains a replaceable BL-5C-style lithium-ion pack interface with wired charging, one NXP SE050E2, QFN BLE and local trusted verification, with Qi, NFC and vibration removed. Full power/RF/audio/isolation qualification, actual assembly sourcing and production firmware remain open. The C0/B0 material below is preserved history. Candidate 3.1 has been reviewed separately and remains unaccepted; no fabrication or paid action was made.
The corrected Rev C cloud retry has **finished at 95% routing and is rejected for release**. Native KiCad after refill found 30 open connections and 29 short-circuit findings in candidate 4.1, plus a failed antenna keepout layer transformation. A comparison candidate also fails. [Returned-layout evidence and next action](evidence/2026-11-16/quilter-retry-01-return/README.md) · [Checked clean retry input](rev-c/quilter-retry-01/README.md). The earlier 93% return is preserved. No result was imported into live B0 and no replacement run or order was started by this review.

The preserved live editor still holds the **[standalone Rev B prototype](rev-b/README.md)**: a rectangular 70 × 45 mm SMD board using Safe 7 core ICs, with audio, microSD, independent debug interfaces and sourceable display/battery candidates. It contains **296 electrical components, 14 probe pads and four mounting holes**. The historical complete-board FreeRouting result has **280 open connections, 33 layout errors and 100 warnings**. [Actual run and final DRC](evidence/2026-11-12/autoroute/README.md). **Manufacturing remains blocked.** [Status](rev-b/STATUS.json) · [Actual B0 images and results](evidence/2026-11-12/README.md)

## Open the preserved MCP PCB

The current launcher/MCP deliberately remain pinned to preserved B0; they do not edit the C1 cloud input. Open the [C1 project](rev-c1/voicevault-standalone-c1.kicad_pro) explicitly to inspect it. Run `./hardware/open` from the repository for B0. It opens only the PCB editor required for MCP and reuses an existing copy. This computer previously ran out of memory when several CAD/emulator windows were opened together. Keep the schematic/3D/emulators closed during heavier jobs. The older `--all` launcher targets the historical Rev A demonstration and is not the active B0 workflow.

Installed tools: **KiCad 10.0.8, ngspice 47, Renode 1.17.0, QEMU 9.2.4**, **Freerouting 2.5.0** and **kicad-tools 0.29.0** for bounded routing studies. [Exact tool records](reference/tools.json)

KiCad editor interaction uses MCP through official IPC. Native KiCad generation/exports/ERC/DRC and ngspice runs use direct command-line tools. This keeps inputs, outputs and failures reproducible and inspectable without requiring a separate MCP server for every executable. Renode currently lacks the required STM32U5G peripherals; QEMU runs CPU-only diagnostics. Neither is a qualified full-device emulator.

## Local KiCad MCP

The enabled stdio server `voicevault-kicad`, launched by `hardware/mcp`, uses the official MCP SDK and KiCad Python IPC bindings. It checks the exact active B0 board path and exposes status, footprint positions, named nets, an undoable footprint move and save. It does not expose a schematic-editing API or program a physical MCU.

The environment uses **managed CPython 3.12.14**, independent of system Python updates. Recreate it with:

```sh
python3 hardware/tools/setup_design_env.py
python3 hardware/tools/setup_kicad.py --enable-api
```

This requires `uv` and KiCad with its symbol/footprint/3D library extensions. Register the absolute `hardware/mcp` launcher with `codex mcp add voicevault-kicad -- /absolute/path/to/hardware/mcp`, then run `./hardware/open`. An existing Codex session may need reopening to discover newly registered tools; the MCP stdio connection can also be verified directly. The local IPC socket is under the KiCad Flatpak cache at `vv-pcb/kicad/api.sock`. No network listener is used by MCP.

The latest live check read **314 footprints and 199 named nets** from the open B0 editor. Evidence is stored with the dated B0 results. The earlier 30-footprint Rev A MCP result is historical.

Current 2D rendering uses **software/Cairo** to avoid the recurring OpenGL loader error. GPU/OpenGL startup is not claimed fixed. The setup helper saves library tables and first-run choices. The native generator now attaches rear-side footprints to the board before flipping them; doing that in the opposite order triggered KiCad's bundled Python 3.14 crash. This is separate from the pinned MCP Python environment.

## Available checks

```sh
./hardware/check --design-only --spice
```

Results and raw logs go to `.lab-runs/hardware/standalone-b0/`. The checks compare the actual native schematic and copper-pad net assignments, verify independent ST ball/function data, run ERC/DRC, test the antenna keepout with deliberately forbidden copper on a copy, exercise the copper-import guard on deliberately valid/invalid proposals, execute **799 ngspice passive/static cases** when `--spice` is selected, and compute a clearly labeled power-allocation study.

`--design-only` exits 0 when those available checks pass, **while keeping the manufacturing verdict blocked**. Without it, exit 2 means manufacturing is blocked. Exit 1 means an available check failed. DRC's list is capped, so remaining routing work is counted from KiCad's full ratsnest rather than the first 499 listed items.

Install ngspice 47 on another host, or point `VOICEVAULT_NGSPICE` to its executable. The scripts prefer this computer's verified cached installation when present. [SPICE models and limits](rev-b/SPICE_RESULTS.md) · [Power/circuit review](rev-b/CIRCUIT_REVIEW.md)

The latest whole-board run used the official, unmodified **FreeRouting 2.5.0 JAR on OpenJDK 25.0.4.1**, with bounded memory/CPU use and a 30-minute application deadline. It saved an SES at the deadline. KiCad’s native SES reader decoded it on a copy; a copper-only kipy transaction applied the complete result to the live board. The earlier timed-out studies were not applied. The current global result fails native DRC and is an unfinished checkpoint. Autorouting does not qualify BGA escape geometry, RF matching, return planes, power loops or a manufacturing stackup.

## Target and qualification

[Active B0 target](rev-b/target.json) is **STM32U5G9ZJJ6Q UFBGA144**. [Earlier bench reference](reference/target.json) is the DK2's **STM32U5G9ZJT6Q LQFP144**. Keep those identities distinct. The B0 revision, option bytes, entropy, audio/DMA interrupts, forbidden-access denial, clocks, supply behavior, radio isolation, acoustics, RF, charging and thermals remain unmeasured.

The software's hardware-evidence contract rejects absent models, warning-producing register accesses, missing samples/interrupts/denials and timeouts. A synthetic trace is a test of the checker, not evidence about physical silicon. CPU-only crypto/Opus memory results remain scoped to their recorded configurations.

## Historical Rev A carrier

`hardware/rev-a/` preserves the earlier 150 × 120 mm cabled DK2 carrier, module BOM and wiring plan. It is not the custom B0 device and is also unrouted. Run `./hardware/check --rev-a --design-only` for its 22 older circuit cases and actual Renode missing-peripheral negative control. [2026-11-11 evidence](evidence/2026-11-11/README.md) preserves those results. The [NUCLEO-U5A5 assessment](reference/NUCLEO_U5A5_ASSESSMENT.md) remains a reference comparison, not the active compute module.

## Assembly

[Manufacturing cost research](rev-b/MANUFACTURING_COST.md) compares public capabilities/fees for four assemblies delivered to Sweden. A cheapest delivered supplier is not established. Routing proceeds against provisional published constraints while quotations are deferred.

The [B0 circuit inventory](rev-b/circuit-inventory.csv) is not an approved assembly BOM. Exact part/variant acceptance, HDI stackup, land patterns, routing, power/thermal review, DFM/CPL, fixtures and physical qualification remain open. Batteries and other external assemblies need explicitly agreed handling; a populated PCB is not automatically a complete enclosed device. Nothing has been ordered or submitted for manufacture.

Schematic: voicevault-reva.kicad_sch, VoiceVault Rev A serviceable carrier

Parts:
C1: 100n 16V; C_0603_1608Metric
C2: 10u 16V; C_0805_2012Metric
C3: 22u 16V; C_1210_3225Metric
C4: 220u 10V HP left; CP_Radial_D6.3mm_P2.50mm
C5: 220u 10V HP right; CP_Radial_D6.3mm_P2.50mm
J1: DK2 CN1 extension; PinHeader_2x20_P2.54mm_Vertical
J2: DK2 CN4 digital; PinHeader_1x10_P2.54mm_Vertical
J3: DK2 CN6 digital; PinHeader_1x08_P2.54mm_Vertical
J4: DK2 CN7 analog; PinHeader_1x06_P2.54mm_Vertical
J5: DK2 CN5 power; PinHeader_1x08_P2.54mm_Vertical
J6: WM8960 digital harness; PinHeader_1x12_P2.54mm_Vertical
J7: nRF52840 radio harness; PinHeader_1x06_P2.54mm_Vertical
J8: TROPIC Click harness; PinHeader_1x07_P2.54mm_Vertical
J9: OPTIGA Trust M harness; PinHeader_1x04_P2.54mm_Vertical
J10: microSD SPI harness; PinHeader_1x06_P2.54mm_Vertical
J11: Codec analog harness; PinHeader_1x06_P2.54mm_Vertical
J12: CTIA headset harness; PinHeader_1x04_P2.54mm_Vertical
J13: Qi receiver output; PinHeader_1x02_P2.54mm_Vertical
J14: BQ24074 charger harness; PinHeader_1x04_P2.54mm_Vertical
J15: 5V regulator harness; PinHeader_1x04_P2.54mm_Vertical
J16: Local update button; PinHeader_1x02_P2.54mm_Vertical
R1: 2.2k mic bias; R_0603_1608Metric
R2: 10k mute sense; R_0603_1608Metric
R3: 47k SD deselect; R_0603_1608Metric
R4: 10k SE deselect; R_0603_1608Metric
SW1: Physical mic disconnect; SW_CK_JS202011CQN_DPDT_Straight

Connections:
3V3: C1.1 (3V3), C2.1 (3V3), J1.2 (3V3), J1.4 (3V3), J1.6 (3V3), J1.40 (3V3), J5.4 (3V3), J6.1 (3V3), J8.1 (3V3), J9.1 (3V3), J10.1 (3V3), R2.1 (3V3), R3.1 (3V3), R4.1 (3V3)
5V_SYS: C3.1 (5V_SYS), J5.5 (5V_SYS), J6.3 (5V_SYS), J7.1 (5V_SYS), J15.3 (5V_SYS)
AUDIO_ADC: J1.20 (AUDIO_ADC), J6.11 (AUDIO_ADC)
AUDIO_BCLK: J3.5 (AUDIO_BCLK), J6.7 (AUDIO_BCLK)
AUDIO_DAC: J2.1 (AUDIO_DAC), J6.10 (AUDIO_DAC)
AUDIO_FS: J1.14 (AUDIO_FS), J6.8 (AUDIO_FS), J6.9 (AUDIO_FS)
AUDIO_MCLK: J3.8 (AUDIO_MCLK), J6.6 (AUDIO_MCLK)
CHARGER_OUT: J14.3 (CHARGER_OUT), J15.1 (CHARGER_OUT)
CODEC_MIC: J11.5 (CODEC_MIC), R1.2 (CODEC_MIC), SW1.2 (CODEC_MIC)
CTRL_SCL: J2.10 (CTRL_SCL), J6.5 (CTRL_SCL), J9.4 (CTRL_SCL)
CTRL_SDA: J2.9 (CTRL_SDA), J6.4 (CTRL_SDA), J9.3 (CTRL_SDA)
GND: C1.2 (GND), C2.2 (GND), C3.2 (GND), J1.1 (GND), J1.3 (GND), J1.5 (GND), J1.7 (GND), J1.9 (GND), J1.11 (GND), J1.13 (GND), J1.15 (GND), J1.17 (GND), J1.19 (GND), J1.21 (GND), J1.23 (GND), J1.25 (GND), J1.27 (GND), J1.29 (GND), J1.31 (GND), J1.33 (GND), J1.35 (GND), J1.37 (GND), J1.39 (GND), J2.7 (GND), J5.6 (GND), J5.7 (GND), J6.2 (GND), J6.12 (GND), J7.2 (GND), J8.2 (GND), J9.2 (GND), J10.2 (GND), J11.3 (GND), J11.6 (GND), J12.3 (GND), J13.2 (GND), J14.2 (GND), J14.4 (GND), J15.2 (GND), J15.4 (GND), J16.2 (GND), SW1.3 (GND), SW1.4 (GND)
HEADSET_MIC: J12.4 (HEADSET_MIC), SW1.1 (HEADSET_MIC)
HP_L: C4.2 (HP_L), J12.1 (HP_L)
HP_L_RAW: C4.1 (HP_L_RAW), J11.1 (HP_L_RAW)
HP_R: C5.2 (HP_R), J12.2 (HP_R)
HP_R_RAW: C5.1 (HP_R_RAW), J11.2 (HP_R_RAW)
MCU_TX_TO_RADIO: J3.2 (MCU_TX_TO_RADIO), J7.3 (MCU_TX_TO_RADIO)
MICBIAS: J11.4 (MICBIAS), R1.1 (MICBIAS)
MIC_SENSE: J1.10 (MIC_SENSE), R2.2 (MIC_SENSE), SW1.5 (MIC_SENSE)
QI_5V: J13.1 (QI_5V), J14.1 (QI_5V)
RADIO_CREDIT: J4.3 (RADIO_CREDIT), J7.5 (RADIO_CREDIT)
RADIO_PENDING: J4.4 (RADIO_PENDING), J7.6 (RADIO_PENDING)
RADIO_TX_TO_MCU: J3.1 (RADIO_TX_TO_MCU), J7.4 (RADIO_TX_TO_MCU)
SD_CS: J2.3 (SD_CS), J10.3 (SD_CS), R3.2 (SD_CS)
SD_MISO: J4.1 (SD_MISO), J10.6 (SD_MISO)
SD_MOSI: J4.6 (SD_MOSI), J10.5 (SD_MOSI)
SD_SCK: J4.5 (SD_SCK), J10.4 (SD_SCK)
SE_CS: J2.2 (SE_CS), J8.3 (SE_CS), R4.2 (SE_CS)
SE_IRQ: J1.8 (SE_IRQ), J8.7 (SE_IRQ)
SE_MISO: J2.5 (SE_MISO), J8.6 (SE_MISO)
SE_MOSI: J2.4 (SE_MOSI), J8.5 (SE_MOSI)
SE_SCK: J2.6 (SE_SCK), J8.4 (SE_SCK)
UPDATE_BUTTON: J1.12 (UPDATE_BUTTON), J16.1 (UPDATE_BUTTON)

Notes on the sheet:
VoiceVault Rev A | DK2 cabled carrier | electrical review draft
Reference STM32U5G9ZJT6Q revision Z. Verify actual DBGMCU ID before bench qualification.
Ports are harness connectors. Follow pin map and module wiring guide. Passive port ERC checks connectivity only.
PCB placement is unrouted. Manufacturing release requires electrical, routing, thermal and bench review.
Radio is untrusted. Only 3.3V UART and credit signals cross the boundary. No audio, reset, SWD or update line.
SW1 common pins 2 and 5. MIC OFF connects 2 to 3, grounds codec input, disconnects headset mic and releases sense.
BQ24074 powered from Qi. Battery plugs into charger directly. Select 500mA input limit and 500mA charging.
5V regulator output feeds DK2 CN5.5 only after correct DK2 power selection. Never parallel bench power supplies.

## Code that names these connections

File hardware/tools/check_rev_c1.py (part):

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
def check_connections(nodes,manifest,pins):
    assert validate(nodes,mcu_package='lqfp')==72
    signals={'PA13':'MCU_SWDIO','PA14':'MCU_SWCLK','PB3':'MCU_SWO','NRST':'MCU_NRST',
             'PC8':'MCU_UART_RX','PC9':'MCU_UART_TX'} | manifest['mcu_signals']
    assert signals.get('PB13')=='SD_SCK_MCU' and 'PC0' not in signals
    expected={}
    function_checks=0
    for pin,info in pins.items():
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
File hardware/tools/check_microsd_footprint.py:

#!/usr/bin/env python3
"""Compare the selected socket's actual native lands with reviewed drawing data.

SD-104031-001 rev B2 sheet 1: KiCad's local origin/view is rotated 180 degrees
relative to the recommended PCB layout. Latest delivered revision and assembly
acceptance are separate gates; the drawing-copy provenance is recorded in Git.
"""
import json
from pathlib import Path
import pcbnew

ROOT=Path(__file__).resolve().parents[2]
DESIGN=ROOT/'hardware/rev-b'

def main():
    footprint=pcbnew.FootprintLoad(str(DESIGN/'VoiceVault_B0.pretty'),'microSD_HC_Molex_104031-0811')
    assert footprint is not None
    expected={str(i+1):[(x,-5.45,.85,1.1)] for i,x in enumerate([-3.105,-2.005,-.905,.195,1.295,2.395,3.495])}
    expected.update({'8':[(4.545,-5.45,.75,1.1)],'9':[(-5.74,.7,1.2,1)],'10':[(-5.74,4.4,1.2,1)],
        'SH':[(-5.565,-5.325,1.55,1.35),(-2.24,5.375,1.9,1.35),(3.73,5.375,1.9,1.35),(5.755,-5.1,1.17,1.8)]})
    actual={}
    for p in footprint.Pads():
        actual.setdefault(p.GetNumber(),[]).append((p.GetPosition().x,p.GetPosition().y,p.GetSize().x,p.GetSize().y))
    integer=lambda values:sorted(tuple(pcbnew.FromMM(v) for v in row) for row in values)
    assert set(actual)==set(expected)
    for number in expected:
        # Library serialization is exact to 1nm; allow 2nm conversion rounding.
        assert all(abs(a-b)<=2 for aa,bb in zip(sorted(actual[number]),integer(expected[number])) for a,b in zip(aa,bb)),number
        assert len(actual[number])==len(expected[number]),number
    board=pcbnew.LoadBoard(str(DESIGN/'voicevault-standalone-b0.kicad_pcb'))
    socket=next(f for f in board.GetFootprints() if f.GetReference()=='J401')
    assert socket.GetValue()=='1040310811' and socket.GetFPID().GetLibItemName()=='microSD_HC_Molex_104031-0811'
    mapping={'1':'SD_DAT2','2':'SD_CS_N','3':'SD_MOSI','4':'SD_3V3','5':'SD_SCK','6':'GND','7':'SD_MISO','8':'SD_DAT1','9':'SD_DETECT_N','10':'GND','SH':'GND'}
    assert {p.GetNumber():p.GetNetname() for p in socket.Pads()}==mapping
    assert len(list(socket.Pads()))==14
    assert socket.GetLayer()==pcbnew.F_Cu
    scratch=pcbnew.BOARD();scratch.Add(footprint)
    footprint.SetOrientationDegrees(socket.GetOrientationDegrees());footprint.SetPosition(socket.GetPosition())
    world=lambda f:sorted((p.GetNumber(),p.GetPosition().x,p.GetPosition().y,p.GetSize().x,p.GetSize().y,p.GetOrientationDegrees()%360) for p in f.Pads())
    for a,z in zip(world(footprint),world(socket)):
        assert a[0]==z[0] and all(abs(x-y)<=2 for x,y in zip(a[1:5],z[1:5])) and abs(a[5]-z[5])<1e-6,'Actual board land differs from reviewed pattern'
    out=ROOT/'.lab-runs/hardware/standalone-b0/microsd-footprint.json'
    result=dict(result='pass',part='Molex 1040310811',drawing='SD-104031-001 rev B2 sheet 1',
        logical_pins=11,physical_pads=14,actual_board_pin_nets_verified=True,actual_board_land_geometry_verified=True,
        normally_open_card_detect_closes_to_ground=True,
        scope='Nominal reviewed land geometry and pin mapping; not latest-revision, sourcing or physical qualification')
    out.parent.mkdir(parents=True,exist_ok=True);out.write_text(json.dumps(result,indent=2)+'\n')
    print(json.dumps(result,indent=2))

if __name__=='__main__':main()
